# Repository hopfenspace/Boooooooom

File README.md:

# Esp prototyping repo

## Documentation

`cargo doc` will fail to compile `esp_idf_sys`, because it requires a specific target:

```bash
cargo doc --target riscv32imc-esp-espidf
```

The resulting documentation will be in `target/riscv32imc-esp-espidf/doc` instead of `target/doc`

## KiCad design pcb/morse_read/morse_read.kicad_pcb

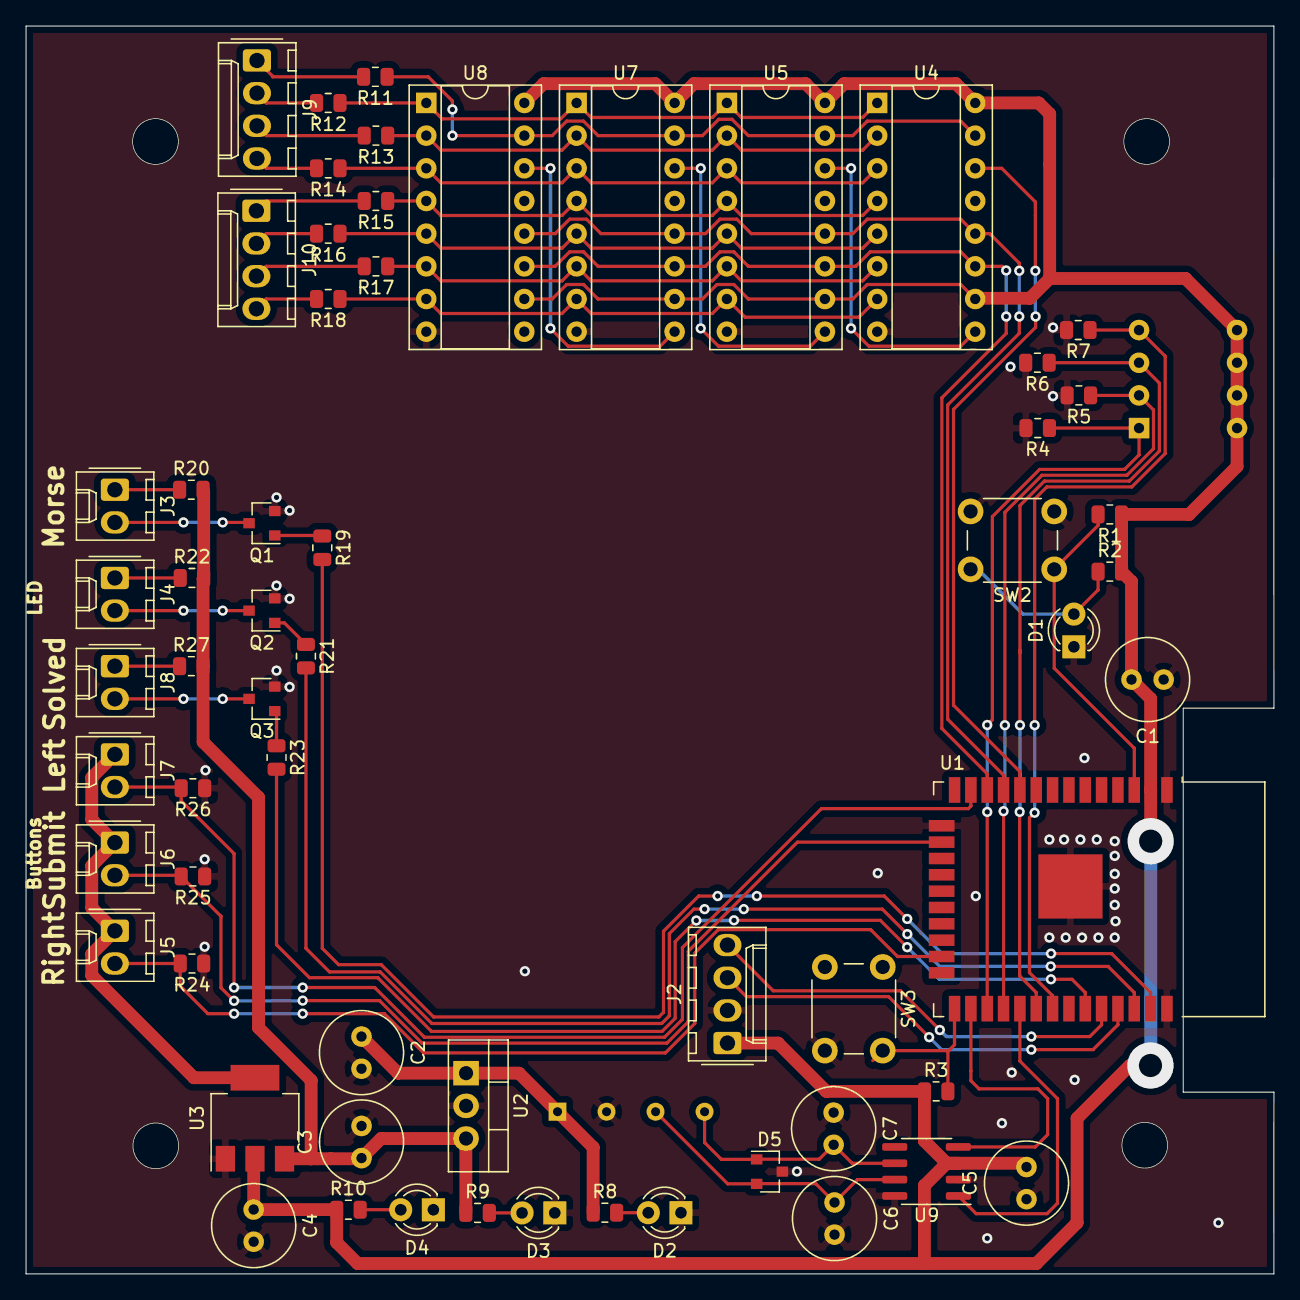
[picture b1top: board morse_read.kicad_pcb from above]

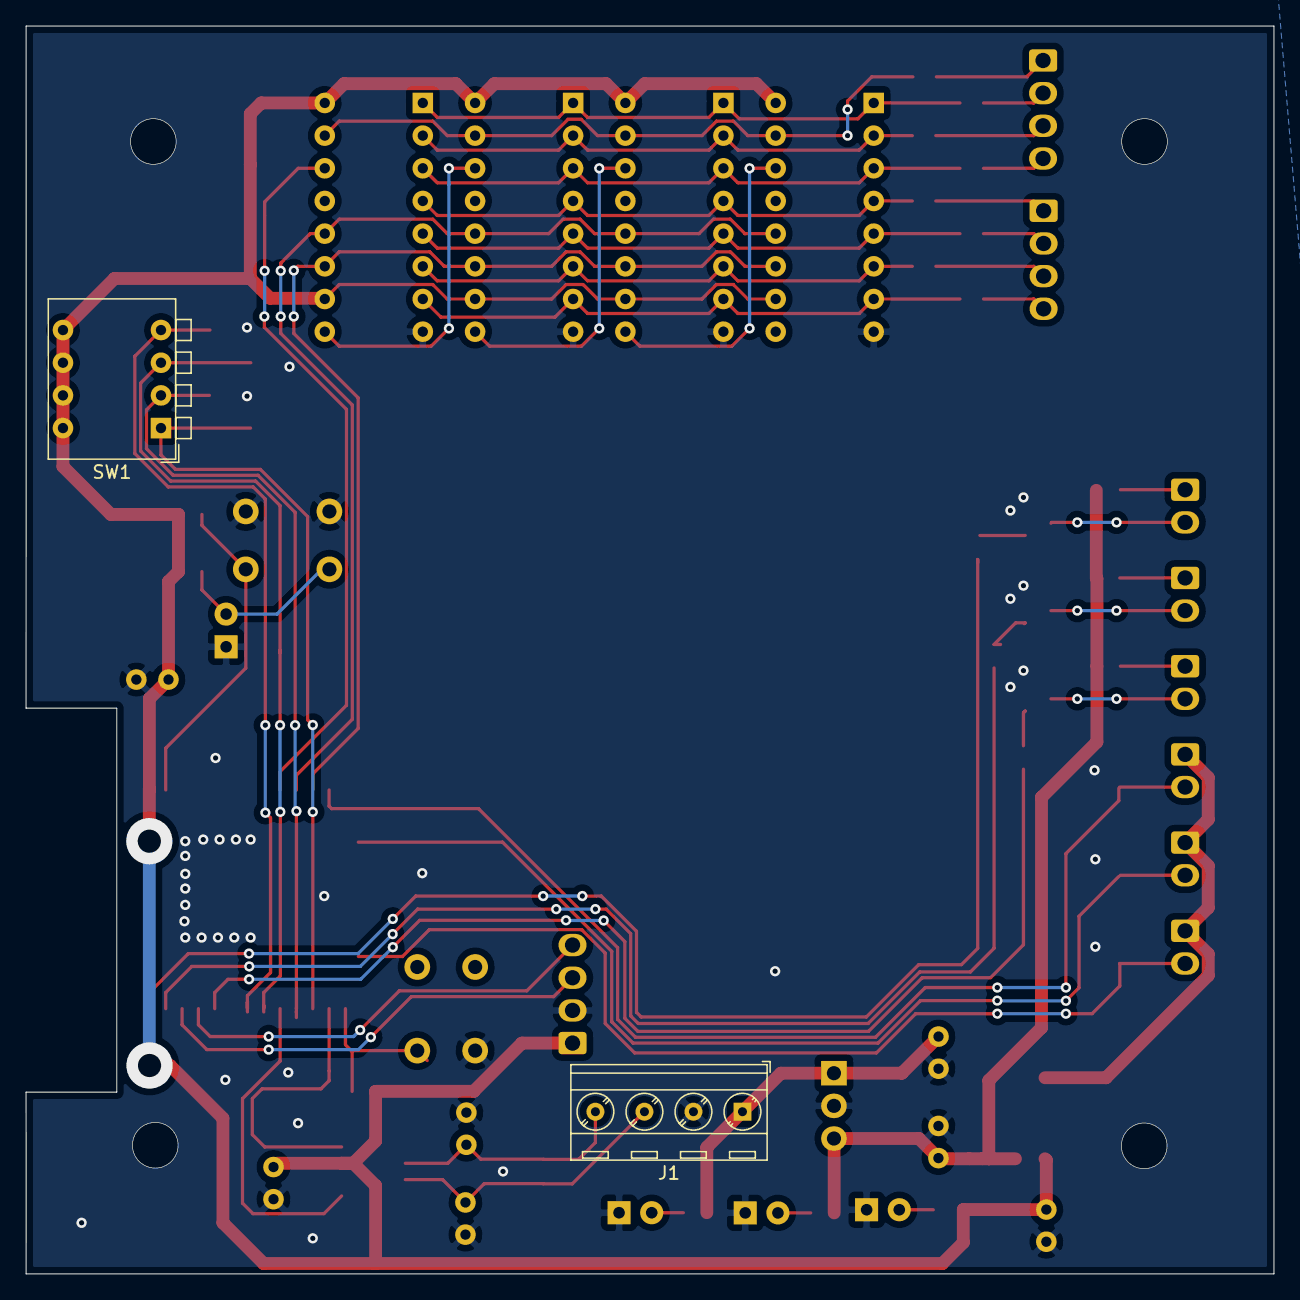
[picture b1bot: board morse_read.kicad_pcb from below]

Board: 2 copper layers, 97.0 x 97.0 mm, 63 parts (2 on the bottom side), 57 nets.

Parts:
C1: 100u; C_Radial_D6.3mm_H11.0mm_P2.50mm
C2, C4: 22uF; C_Radial_D6.3mm_H7.0mm_P2.50mm
C3: 68uF; C_Radial_D6.3mm_H7.0mm_P2.50mm
C5: 100n; C_Radial_D6.3mm_H11.0mm_P2.50mm
C6, C7: 47pF; C_Radial_D6.3mm_H11.0mm_P2.50mm
D1, D2, D3, D4: LED; LED_D3.0mm
D5: NUP2105L; SOT-23
J1: Screw_Terminal_01x04; TerminalBlock_MetzConnect_Type086_RT03404HBLC_1x04_P3.81mm_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
J2, J9, J10: Conn_01x04_Female; Molex_KK-254_AE-6410-04A_1x04_P2.54mm_Vertical
J3, J4, J5, J6, J7, J8: Conn_01x02_Female; Molex_KK-254_AE-6410-02A_1x02_P2.54mm_Vertical
Q1, Q2, Q3: AO3400A; SOT-23
R1, R3, R4, R5, R6, R7, R24, R25, R26: 10k; R_0805_2012Metric
R2, R10: 56; R_0805_2012Metric
R8: 510; R_0805_2012Metric
R9: 180; R_0805_2012Metric
R11, R12, R13, R14, R15, R16, R17, R18, R20, R22: 150; R_0805_2012Metric
R19, R21, R23: 330; R_0805_2012Metric
R27: 91; R_0805_2012Metric
SW1: SW_DIP_x04; SW_DIP_SPSTx04_Piano_CTS_Series194-4MSTN_W7.62mm_P2.54mm
SW2, SW3: SW_Push_Dual; SW_PUSH_6mm
U1: ESP32-WROOM-32D; ESP32-WROOM-32
U2: LM7805_TO220; TO-220-3_Vertical
U3: AMS1117-3.3; SOT-223-3_TabPin2
U4, U5, U7, U8: 74HC595; DIP-16_W7.62mm_Socket
U9: SN65HVD230; SOIC-8_3.9x4.9mm_P1.27mm

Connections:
+3V3: C1.2, C4.1, C5.2, J2.1, J5.1, J6.1, J7.1, R1.1, R2.2, R3.1, R10.1, SW1.5, SW1.6, SW1.7, SW1.8, U1.2, U3.2, U4.10, U4.16, U5.10, U5.16, U7.10, U7.16, U8.10, U8.16, U9.3
+5V: C3.1, R9.1, R20.2, R22.2, R27.2, U2.3, U3.3
+12V: C2.1, J1.1, R8.1, U2.1
/CAN_H: C6.1, D5.2, J1.3, U9.7
/CAN_L: C7.2, D5.1, J1.4, U9.6
/CRX: U1.26, U9.4
/CTX: U1.29, U9.1
/DIP_1: R4.1, SW1.1, U1.27
/DIP_2: R5.1, SW1.2, U1.28
/DIP_3: R6.1, SW1.3, U1.30
/DIP_4: R7.1, SW1.4, U1.31
/Left_Button: J7.2, R26.2, U1.13
/Morse_LED: R19.2, U1.37
/RCLK: U1.11, U4.12, U5.12, U7.12, U8.12
/RX: J2.4, U1.34
/Right_Button: J5.2, R24.2, U1.23
/SER: U1.10, U4.14
/SRCLK: U1.12, U4.11, U5.11, U7.11, U8.11
/Shiftregister/QA: R11.1, U4.15, U5.15, U7.15, U8.15
/Shiftregister/QB: R12.1, U4.1, U5.1, U7.1, U8.1
/Shiftregister/QC: R13.1, U4.2, U5.2, U7.2, U8.2
/Shiftregister/QD: R14.1, U4.3, U5.3, U7.3, U8.3
/Shiftregister/QE: R15.1, U4.4, U5.4, U7.4, U8.4
/Shiftregister/QF: R16.1, U4.5, U5.5, U7.5, U8.5
/Shiftregister/QG: R17.1, U4.6, U5.6, U7.6, U8.6
/Shiftregister/QH: R18.1, U4.7, U5.7, U7.7, U8.7
/Solved_LED: R23.2, U1.33
/Strike_LED: R21.2, U1.36
/Submit_Button: J6.2, R25.2, U1.16
/TX: J2.3, U1.35
GND: C1.1, C2.2, C3.2, C4.2, C5.1, C6.2, C7.1, D1.1, D2.1, D3.1, D4.1, D5.3, J1.2, J2.2, Q1.2, Q2.2, Q3.2, R4.2, R5.2, R6.2, R7.2, R24.1, R25.1, R26.1, SW2.2, SW3.2, U1.1, U1.15, U1.38, U1.39, U2.2, U3.1, U4.8, U5.8, U7.8, U8.8, U9.2, U9.8
unnamed: D1.2, R2.1, SW2.1
unnamed: D2.2, R8.2
unnamed: D3.2, R9.2
unnamed: D4.2, R10.2
unnamed: J3.1, R20.1
unnamed: J3.2, Q1.3
unnamed: J4.1, R22.1
unnamed: J4.2, Q2.3
unnamed: J8.1, R27.1
unnamed: J8.2, Q3.3
unnamed: J9.1, R11.2
unnamed: J9.2, R12.2
unnamed: J9.3, R13.2
unnamed: J9.4, R14.2
unnamed: J10.1, R15.2
unnamed: J10.2, R16.2
unnamed: J10.3, R17.2
unnamed: J10.4, R18.2
unnamed: Q1.1, R19.1
unnamed: Q2.1, R21.1
unnamed: Q3.1, R23.1
unnamed: R1.2, SW2.1, U1.3
unnamed: R3.2, SW3.1, U1.25
unnamed: U4.9, U5.14
unnamed: U5.9, U7.14
unnamed: U7.9, U8.14

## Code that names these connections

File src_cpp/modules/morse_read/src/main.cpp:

#include <map>
#include <string>
#include <vector>
#include <functional>
#include <tuple>
#include <stdlib.h>

#include <Arduino.h>
#include <CAN.h>

#include "wordlist.h"

#define MORSE_LED 17
#define STRIKE_LED 18
#define SOLVED_LED 19

#define LEFT_BUTTON 15
#define RIGHT_BUTTON 16
#define SUBMIT_BUTTON 2

#define CAN_RX 4
#define CAN_TX 5


enum difficulty{EASY=320, NORMAL=160, HARD=80, EXPERT=40, PREPARE_2_DIE=20};

std::map<char, std::string> morseCode = {
    {'a', ".-"}, {'b', "-..."}, {'c', "-.-."}, {'d', "-.."}, {'e', "."}, {'f', "..-."}, {'g', "--."}, 
    {'h', "...."}, {'i', ".."}, {'j', ".---"}, {'k', "-.-"}, {'l', ".-.."}, {'m', "--"}, {'n', "-."},
    {'o', "---"}, {'p', ".--."}, {'q', "--.-"}, {'r', ".-."}, {'s', "..."}, {'t', "-"}, {'u', "..-"},
    {'v', "...-"}, {'w', ".--"}, {'x', "-..-"}, {'y', "-.--"}, {'z', "--.."}, {'1', ".----"}, 
    {'2', "..---"}, {'3', "...--"}, {'4', "....-"}, {'5', "....."}, {'6', "-...."}, {'7', "--..."}, 
    {'8', "---.."}, {'9', "----."}, {'0', "-----"}, {' ', "/"}
};

int unitTime;
boolean solved;
std::string chosenOne;
std::string current;
std::vector<std::string> wordlist;
std::vector<int> frequencies;
std::map<std::string, int> wordlistLookup;

int jobCounter = 0;
std::vector<std::tuple<int, int, std::function<void()>>> jobs;


void addJob(unsigned long execution_time, std::function<void()> callback) {
    jobs.push_back(std::make_tuple(jobCounter, execution_time, callback));
    jobCounter++;
}

std::function<void()> turnLEDOn(int nextExecutionDelta);
std::function<void()> turnLEDOn(int nextExecutionDelta) {
    return [nextExecutionDelta]() {
        digitalWrite(MORSE_LED, 1);
        addJob(millis() + nextExecutionDelta, turnLEDOn(nextExecutionDelta));
    };
}

std::function<void()> turnLEDOff(int nextExecutionDelta);
std::function<void()> turnLEDOff(int nextExecutionDelta) {
    return [nextExecutionDelta](){
        digitalWrite(MORSE_LED, 0);
        addJob(millis() + nextExecutionDelta, turnLEDOff(nextExecutionDelta));
    };
}

std::vector<std::string> translate_to_morse(std::string sentence, boolean end_with_pause = true) {
    std::vector<std::string> translated;

    for(int i = 0; i < sentence.length(); i++) {
        sentence[i] = tolower(sentence[i]);
        translated.push_back(morseCode[sentence[i]]);
    }
    if (end_with_pause && translated[translated.size()-1] != "/") {
        translated.push_back("/");
    }
    return translated;
}

void write_morse(std::string sentence) {
    std::vector<std::string> translated = translate_to_morse(sentence);

    int unitCounter = 0;
    for(int i = 0; i < translated.size(); i++) {
        for(int j = 0; j < translated[i].size(); j++) {
            if(translated[i][j] == '.') {
                // Dot is 1 unit
                unitCounter++;
            } else if(translated[i][j] == '-') {
                // Dash is 3 units
                unitCounter += 3;
            } else if(translated[i][j] == '/') {
                // Word pause is 7 units
                unitCounter += 7;
            }
            if(j != translated[i].size() - 1) {
                // Intra character pause is 1 unit
                unitCounter++;
            } else {
                if(translated[i][j] != '/' && i != translated.size()-1 && translated[i+1] != "/") {
                    // Current char is no word pause and next char is no word pause
                    // Inter character pause is 3 units
                    unitCounter += 3;
                }
            }
        }
    }

    int nextExecutionDelta = unitTime * unitCounter;

    int counter = 0;
    for(int i = 0; i < translated.size(); i++) {
        for(int j = 0; j < translated[i].size(); j++) {
            if(translated[i][j] == '.') {
                addJob(millis() + counter*unitTime, turnLEDOn(nextExecutionDelta));
                counter++;
            } else if(translated[i][j] == '-') {
                addJob(millis() + counter*unitTime, turnLEDOn(nextExecutionDelta));
                counter += 3;
            } else if(translated[i][j] == '/') {
                addJob(millis() + counter*unitTime, turnLEDOff(nextExecutionDelta));
                counter += 7;
            }
            if(j != translated[i].size()-1) {
                // Intra character pause
                addJob(millis() + counter*unitTime, turnLEDOff(nextExecutionDelta));
                counter++;
            } else {
                if(translated[i][j] != '/' && i != translated.size()-1 && translated[i+1] != "/") {
                    // Inter character pause
                    addJob(millis() + counter*unitTime, turnLEDOff(nextExecutionDelta));
                    counter += 3;
                }
            }
        }
    }
}

void handleLeft() {
    int index = 0;
    for (int i = 0; i < wordlist.size(); i++) {
        if (current == wordlist[i]) {
            index = i;
            break;
        }
    }
    if (index > 0) {
        current = wordlist[index-1];
    }
    Serial.printf("Current word: %s\n", current.c_str());
}

void irqLeft() {
    addJob(millis(), handleLeft);
}

void handleRight() {
    int index = 0;
    for (int i = 0; i < wordlist.size(); i++) {
        if(current == wordlist[i]) {
            index = i;
            break;
        }
    }
    if(index != wordlist.size()-1) {
        current = wordlist[index+1];
    }
    Serial.printf("Current word: %s\n", current.c_str());
}

void irqRight() {
    addJob(millis(), handleRight);
}

void irqSubmit() {
    if (current == chosenOne) {
        solved = true;
    } else {
        // TODO: Push job: send strike
        addJob(millis(), [](){
            digitalWrite(STRIKE_LED, 1);
        });
        addJob(millis()+300, []() {
            digitalWrite(STRIKE_LED, 0);
        });
    }
}

void loop() {
    if (solved) {
        digitalWrite(SOLVED_LED, 1);
        return;
    }

    // Process jobs
    std::vector<int> eraseList;
    for(int i = 0; i < jobs.size(); i++) {
        if(std::get<1>(jobs[i]) <= millis()) {
            std::get<2>(jobs[i])();
            eraseList.push_back(std::get<0>(jobs[i]));
        }
    }
    // Delete elements from jobs that are already executed
    for(int i = 0; i < eraseList.size(); i++) {
        int index = 0;
        for (int x = 0; x < jobs.size(); x++) {
            if(std::get<0>(jobs[x]) == eraseList[i]) {
                index = x;
                break;
            }
        }
        jobs.erase(jobs.begin() + index);
    }
}

void setup_game(difficulty difficulty, int possibleWordCount) {
    attachInterrupt(digitalPinToInterrupt(LEFT_BUTTON), irqLeft, RISING);
    attachInterrupt(digitalPinToInterrupt(RIGHT_BUTTON), irqRight, RISING);
    attachInterrupt(digitalPinToInterrupt(SUBMIT_BUTTON), irqSubmit, RISING);

    unitTime = difficulty;
    if (difficulty >= 160) {
        std::vector<std::string> words5;
        for(auto word: availableWords) {
            if (word.length() == 5) {
                words5.push_back(word);
            }
        }
        int start = words5.size() - rand() % words5.size() - possibleWordCount;
        for(int i = start; i < start + possibleWordCount; i++) {
            wordlist.push_back(words5[i]);
        }
    } else {
        int start = availableWords.size() - rand() % availableWords.size() - possibleWordCount;
        for(int i = start; i < start + possibleWordCount; i++) {
            wordlist.push_back(availableWords[i]);
        }
    }

    while(frequencies.size() != possibleWordCount) {
        frequencies.push_back(rand() % 9000 + 1000);
    }

    std::sort(wordlist.begin(), wordlist.end());
    std::sort(frequencies.begin(), frequencies.end());

    for(int i = 0; i < possibleWordCount; i++) {
        wordlistLookup.insert(std::pair<std::string, int>(wordlist[i], frequencies[i]));
    }

    current = wordlist[rand() % wordlist.size()];
    chosenOne = wordlist[rand() % wordlist.size()];

    for(int i = 0; i < possibleWordCount; i++) {
        Serial.printf("Word: %s; Frequency: %d\n", wordlist[i].c_str(), frequencies[i]);
    }

    Serial.printf("Chosen Word: %s, its frequency: %d\n", chosenOne.c_str(), wordlistLookup[chosenOne]);
}

void setup() {
    Serial.begin(115200);

    pinMode(MORSE_LED, OUTPUT);
    pinMode(STRIKE_LED, OUTPUT);
    pinMode(SOLVED_LED, OUTPUT);

    pinMode(LEFT_BUTTON, INPUT);
    pinMode(RIGHT_BUTTON, INPUT);
    pinMode(SUBMIT_BUTTON, INPUT);

    Serial.println("Setting up CAN");
    CAN.setPins(CAN_RX, CAN_TX);
    while(!CAN.begin(1E6)) {
        Serial.println("CAN startup failed, retrying in 1 second");
        delay(1000);
    }
    Serial.println("CAN set up successfully");

    Serial.println("Changing seed of srand");
    srand(esp_random());

    Serial.println("Initialization complete");

    Serial.println("Setting up game");
    setup_game(NORMAL, 16);

    solved = false;
    Serial.println("Game is ready");

    Serial.println("Starting Game");
    write_morse(chosenOne);
}

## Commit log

2021-10-16 Initialized project
2021-10-16 Added schematic for generic powersupply of the modules
2021-10-22 Initialized project structure
2021-10-22 Implemented first (incomplete) version of morse_read
2021-10-22 Implemented 7648 shift register
2021-10-22 Added lib file for morse output
2021-10-22 Used morse lib
2021-10-22 Implemented a single seven-segment display using the shift register
2021-10-22 Added two missing sleeps for clock cycles
2021-10-22 Used constructor arguments to set initial pin value
2021-10-24 First kind of working draft of can module
2021-10-25 Replaced register manipulation with espressif's hal
2021-10-25 Fixed typos
2021-10-25 Used strings in read/write instead of ints
2021-10-25 Fixed pointer to _onReceive
2021-10-26 Implemented morse_read in cpp
2021-10-27 Moved can module
2021-10-29 Added EventLoop lib
2021-10-29 Created mp binding for esp-idf's can driver
2021-10-30 Tweaked esp-idf's source to enable a custom interupt handler
2021-10-30 Tweaked receive's return value to match transmit's arguments
2021-10-30 Added README.md for can module
2021-10-30 Moved EventLoop to its own library dir
2021-10-30 Moved import of queue to cpp
2021-10-30 Implemented first draft of BMP, readOnly
2021-10-30 Started BMP library
2021-10-31 test
2021-10-31 deleted testing
2021-10-31 backplane + frontpanel missing: NE555 + multiplexing
2021-11-01 PCB completed exept Multiplexer and Frontbuttons & LED scematics updated
2021-11-02 Implemented basic requesting of data
2021-11-03 Added send and req methods for BMP
2021-11-03 PCB update new size 97*97 mm
2021-11-03 Added clock and multiplexer
2021-11-03 Added send for MODULE_INFO, fixed constructPacketId
2021-11-04 Added a small handbook for building the custom mp
2021-11-04 Implemented an async version of BMP
2021-11-04 Extended readme for Arch
2021-11-05 Fixed typo
2021-11-05 First version of controller
2021-11-05 Added map to imports
2021-11-05 Added the first raw version of the Simon Says module
2021-11-05 Fixed LABELS send method
2021-11-06 Fixed breaking bugs in bmp
2021-11-06 Fixed refactored code
2021-11-06 Merged sync and async bmp, also added some data convertion
2021-11-06 Added missing underscore
2021-11-06 Added async version of morse
2021-11-06 Implemented th SN74HC595 shift register
2021-11-06 Enforce big endian
2021-11-06 Corrected time conversion to binary
2021-11-06 Deleted module lib files
2021-11-06 Added upgraded lib
2021-11-06 Removed library from module
2021-11-06 Updated SevenSegment to accept both ShiftRegister
2021-11-06 Moved controller to module
2021-11-06 Added async shift register
2021-11-06 Added set_pins
2021-11-06 Added module to update and manage cpp libs
2021-11-06 Added gitignore
2021-11-06 Added cpp gitignores
2021-11-06 Removed schematic as it is included in kicad files
2021-11-06 Added requirements.json for controller
2021-11-06 Added timer
2021-11-07 Added missing map include
2021-11-07 Added a debugging version of Simon Says game to play in console
2021-11-07 Added the first schema plan for the Simon Says module
2021-11-07 Fixed the name tags on the LED button schematic
2021-11-07 Extended .gitignore to ignore KiCAD cache files
2021-11-07 Added missing command
2021-11-09 Added .gitignore in src_cpp modules to ignore list
2021-11-09 Added basic readme for cpp modules
2021-11-09 Fixed bug that made receiving with ids where the LSB is set impossible
2021-11-10 Key of sliced transmissions is now big enough
2021-11-10 Added WiFi connectivity and callback for RTFM
2021-11-10 Created the game class that should use hardware buttons
2021-11-10 Fixed message
2021-11-10 Fixed access to the button's values in the button dict
2021-11-10 Added a small helper method to test the hardware setup
2021-11-10 Added a task which is responsible for LED flashing, fixed previous commit
2021-11-10 Switched to a dynamic color definition
2021-11-10 Added the default LED flashing times
2021-11-10 Added a color definition as base point for further operations
2021-11-10 Replaced the static color setup with a more dynamic button setup
2021-11-10 Added the allocation of emergency buffers
2021-11-10 Fixed the broken interrupt handler
    Note that this is only relevant since Micropython doesn't process
    lambda functions as correct interrupt handlers.
2021-11-10 Added the multi-step stage, i.e. repeating previous colors is mandatory now
2021-11-10 Fixed handler and tasks bugs
2021-11-11 Added the SimonSays core class as new part of the Python library
2021-11-11 Removed the SimonSays core class from the bomb module's main file
2021-11-11 Added the first version of the HTML manual generation
2021-11-11 Added the first version of the manual generation function
2021-11-11 Changed the internal data structure of mappings
2021-11-11 Fixed the manual, removed the old mapping, replaced the seq_len range
2021-11-11 Fixed the console version of simon says accordingly
2021-11-11 Increased the difficulty of PREPARE_2_DIE
2021-11-11 Allowed a flexible number of colored buttons in the manual description
2021-11-11 Replaced the waiting for blink method by a simple method parameter
2021-11-11 Implemented get_max_strikes using the CAN/BMP library
2021-11-11 Replaced the old create_from_pin_ids classmethod
2021-11-11 Fixed little bug in lib code
2021-11-11 Added a seed so Simon Says now produces same results in multiple runs
    The full "seed" to accurately generate the exactly same manual
    page twice is the combination of seed, max_strikes and difficulty!
    Note that the complete output sequence is not affected by the seed,
    only by the level of difficulty, and will therefore differ between runs.
2021-11-11 Added a new wrapper class to manage the actual game and handle requests
2021-11-11 Cleaned up and added the handler methods for the SimonSaysGame class
2021-11-12 Added missing request handler prototypes, an enabled flag and cleaned up
2021-11-12 Changed the difficulty level for IMMORTAL to reflect the changed docs
2021-11-12 Allow a game to be re-played with different sequences by re-seeding
    Note that the deterministic nature of the manual
    and the mappings is not affected by this change!
2021-11-12 Made sync bmp blocking by extending the async one
2021-11-12 Implemented very basic wire module
2021-11-12 Enable multiple request of same type on different targets
2021-11-13 Removed uasyncio.Event to avoid micropython issue #5843
    The behaviour described in this issue would for example break the SyncBMP class.
    https://github.com/micropython/micropython/issues/5843
2021-11-13 Made the debug version a proper extension of sync
2021-11-13 Fixed Module class to work with micropython's uasyncio
    As already stated in 05f961561ed99f202f4502176020b3b6509480b4,
    `uasyncio.Event` can't be used, if it might be the only remaining task.
    Also apparently `uasyncio.Loop.run_forever` doesn't run forever
    but rather stops when there are no tasks remaining.
2021-11-13 Removed reset, added missing async helper implementations
2021-11-13 Moved base module class into lib
2021-11-13 Added some doc
2021-11-13 Fixed huge delay in modules
    Apparently uasyncio is not really async:
    When it sleeps, it sleeps and doesn't care for newly created tasks
    which could run immediately.
2021-11-13 Completed very basic implementation
2021-11-14 Added topdown view for the case
2021-11-14 Reduced duplicate code by replacing sync classes with subclasses
2021-11-14 Drafted controller implementation in python
2021-11-14 Retrieve manual and info
2021-11-16 updated PCB design and added the multiplexer for the 7-segment display
2021-11-16 Added a simple logging method for debugging, moved the tester function
2021-11-16 Enabled the use of the base module for SimonSays module wrapper
2021-11-17 Added the list of pre-defined difficulty names to the bmp lib
2021-11-17 Added a main function (module startup), fixed various little bugs
2021-11-17 Added seed method; made difficulty proper enum
2021-11-17 Created custom exceptions to identify bugs easier
2021-11-17 Changed to esp-idf v4.3.1
2021-11-17 Exposed custom esp errors to python
2021-11-18 Fixed startup problems and timeout exceptions very dirtyly
2021-11-19 Added a small helper library containing utilities not present in MP
2021-11-19 Added explicit gc and pre-allocated memory blocks to reduce fragmenting
2021-11-19 Implemented exploded/defused handlers, adapted the frontends to the button checker
2021-11-19 Enabled the use of the new title() helper function
2021-11-19 Fixed the simon says core to allow pre-checks and full stage checks
2021-11-20 Made on_receive robuster
    - c++ is still way too fast if it sends constantly
    - one message per 0.5ms without any actual python computation seemed fine
2021-11-21 Implemented filtering
2022-10-09 Project setup
2022-10-09 Implemented thin wrapper around esp-idf's twai
2022-10-09 Rustified error handling; Moved twai into own file
2022-10-09 Implemented From for error conversion
2022-10-09 Started workspace and moved twai into own crate
2022-10-09 Rustified message construction and parsing
2022-10-09 Added README.md to note how to build the docs
2022-10-09 Renamed src directory
2022-10-09 Fixed missing directories
2022-10-09 Updated README.md and .gitignore
2022-10-09 Started new library
2022-10-09 Copied enum from specs
2022-10-10 Added rumms-controller
2022-10-10 Implemented bomb transmission unit
2022-10-10 Restructured code, added Master and Slave interfaces
